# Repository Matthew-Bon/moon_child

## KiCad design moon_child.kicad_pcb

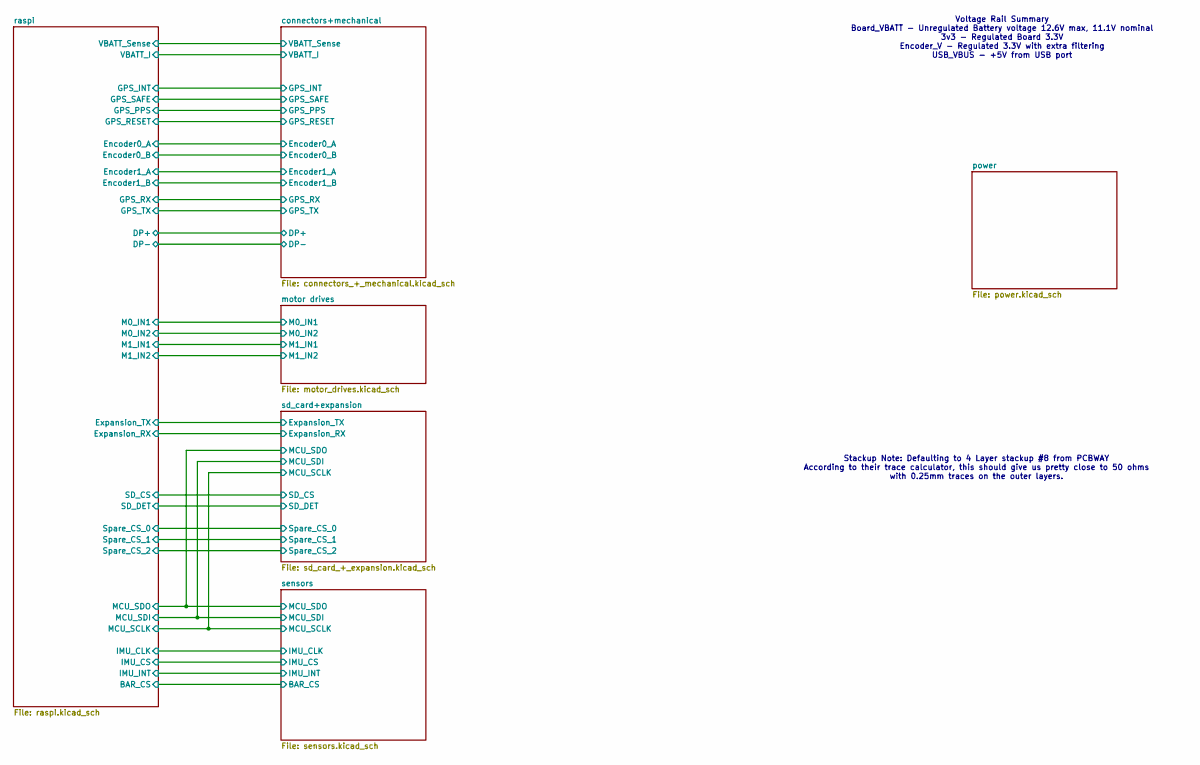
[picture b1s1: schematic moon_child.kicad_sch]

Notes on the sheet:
Voltage Rail Summary Board_VBATT - Unregulated Battery voltage 12.6V max, 11.1V nominal 3v3 - Regulated Board 3.3V Encoder_V - Regulated 3.3V with extra filtering USB_VBUS - +5V from USB port
Stackup Note: Defaulting to 4 Layer stackup #8 from PCBWAY According to their trace calculator, this should give us pretty close to 50 ohms with 0.25mm traces on the outer layers.

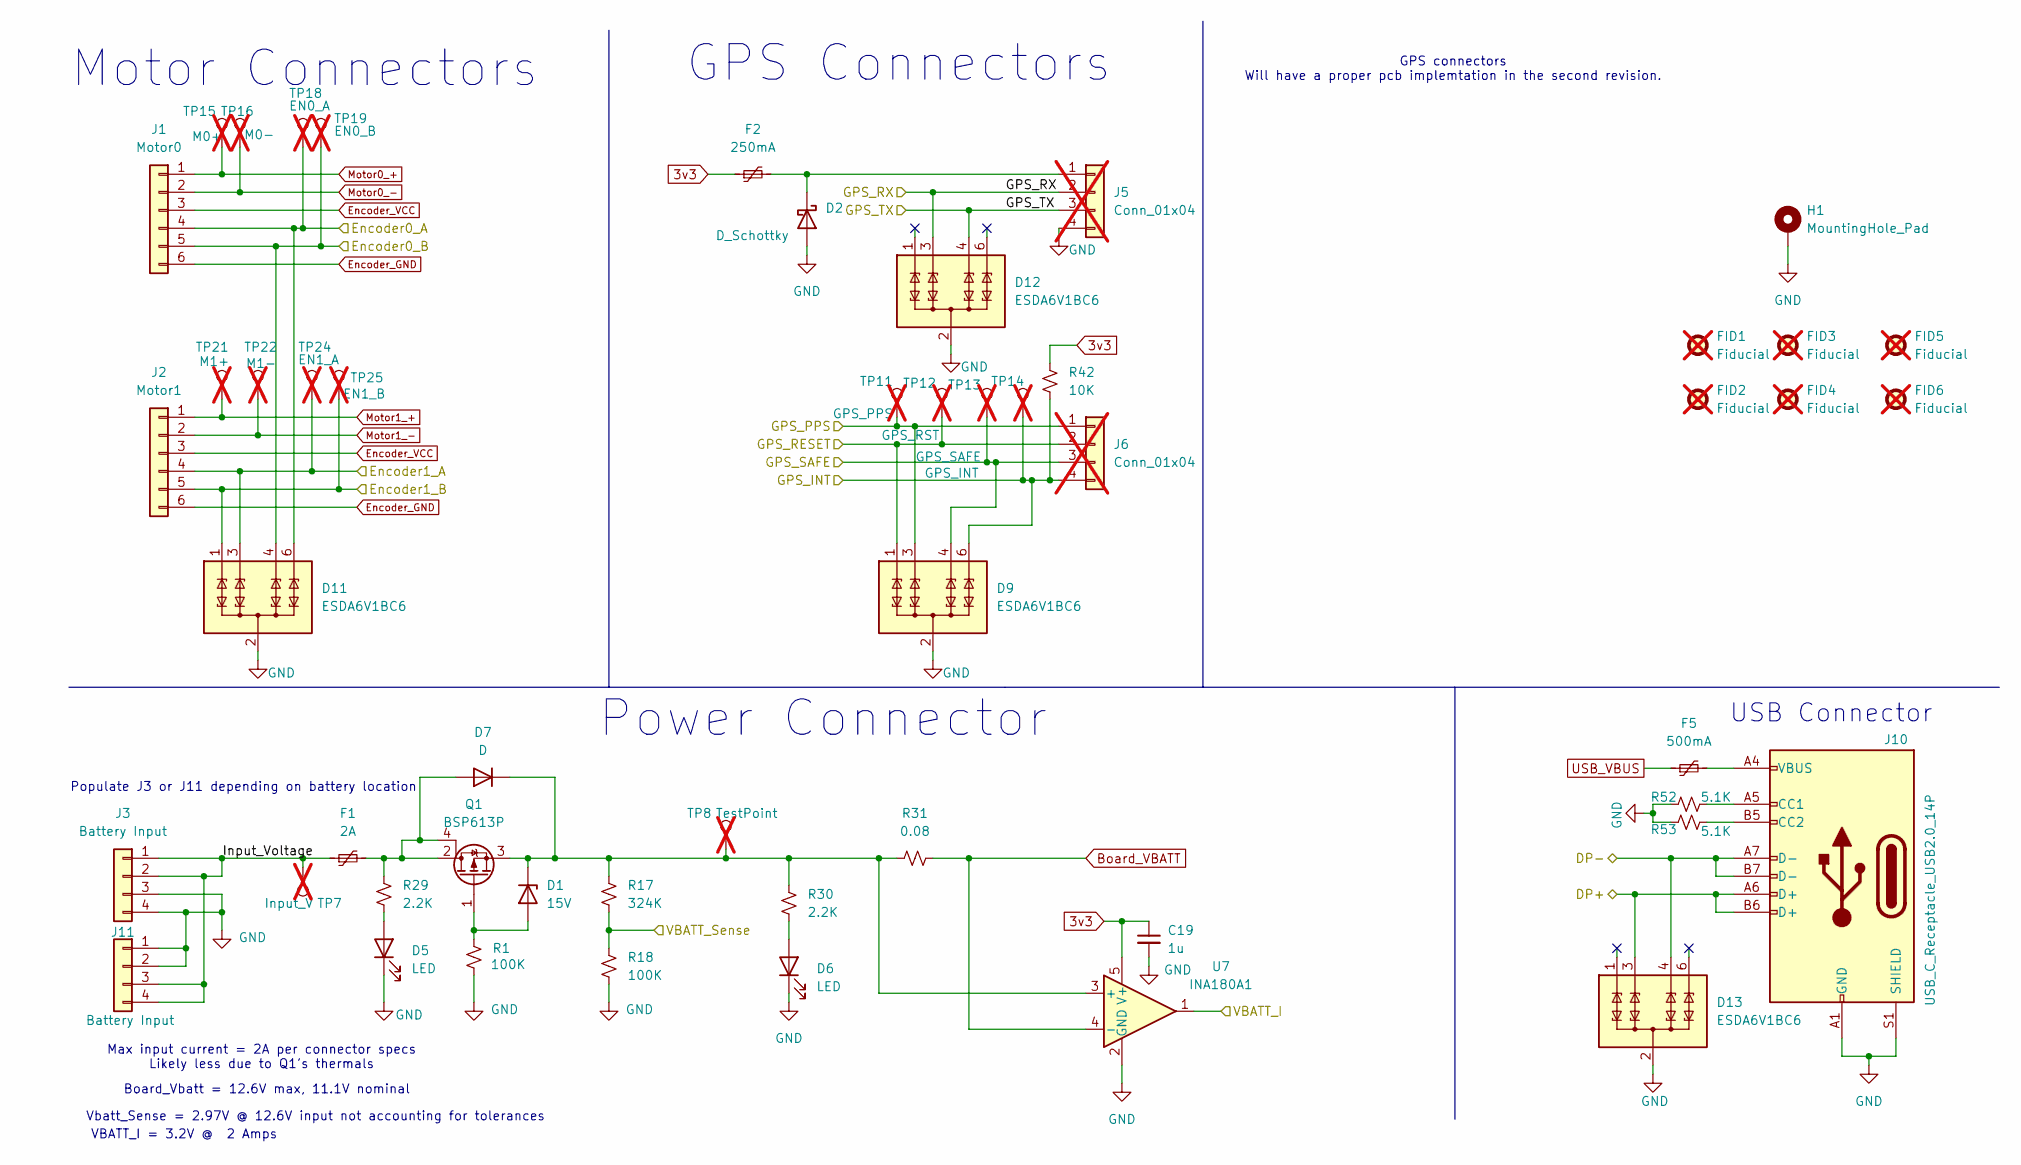
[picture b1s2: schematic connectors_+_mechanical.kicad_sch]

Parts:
C19: 1u; C_0603_1608Metric_Pad1.08x0.95mm_HandSolder; MPN CL10B105KP8NNNC
D1: 15V; D_SOD-323; MPN BZT52C15S-7-F
D2: D_Schottky; D_SOD-123; MPN MBR0530T1G
D5, D6: LED; D_0603_1608Metric_Pad1.05x0.95mm_HandSolder; MPN LTST-C190KFKT
D7: D; D_SMA; MPN S1J-13-F
D9, D11, D12, D13: ESDA6V1BC6; SOT-23-6; MPN ESDA6V1BC6
F1: 2A; Fuse_1206_3216Metric; MPN MF-NSML200/12-2
F2: 250mA; Fuse_1206_3216Metric; MPN 0ZCJ0025FF2E
F5: 500mA; Fuse_1206_3216Metric; MPN 0ZCJ0050AF2E
FID1, FID2, FID3, FID4, FID5, FID6: Fiducial; Fiducial_1mm_Mask2mm; not fitted
H1: MountingHole_Pad; MountingHole_4.3mm_M4_ISO14580_Pad
J1: Motor0; JST_SH_BM06B-SRSS-TB_1x06-1MP_P1.00mm_Vertical; MPN BM06B-SRSS-TB
J2: Motor1; JST_SH_BM06B-SRSS-TB_1x06-1MP_P1.00mm_Vertical; MPN BM06B-SRSS-TB
J3, J11: Battery Input; JST_SH_BM04B-SRSS-TB_1x04-1MP_P1.00mm_Vertical; MPN BM04B-SRSS-TB
J5, J6: Conn_01x04; PinHeader_1x04_P2.54mm_Vertical; not fitted
J10: USB_C_Receptacle_USB2.0_14P; GCT_USB4115-03-C_REVB4; MPN USB4115-03-C
Q1: BSP613P; SOT-223; MPN BSP613PH6327XTSA1
R1, R18: 100K; R_0402_1005Metric; MPN RC0402JR-07100KL
R17: 324K; R_0402_1005Metric; MPN RC0402FR-07324KL
R29, R30: 2.2K; R_0402_1005Metric; MPN RC0402JR-072K2L
R31: 0.08; R_1206_3216Metric; MPN RL1206FR-070R08L
R42: 10K; R_0402_1005Metric; MPN RC0402JR-0710KL
R52, R53: 5.1K; R_0402_1005Metric; MPN RC0402FR-075K1L
TP7: Input_V; TestPoint_Pad_D1.0mm; not fitted
TP8: TestPoint; TestPoint_Pad_D1.0mm; not fitted
TP11: GPS_PPS; TestPoint_Pad_D1.0mm; not fitted
TP12: GPS_RST; TestPoint_Pad_D1.0mm; not fitted
TP13: GPS_SAFE; TestPoint_Pad_D1.0mm; not fitted
TP14: GPS_INT; TestPoint_Pad_D1.0mm; not fitted
TP15: M0+; TestPoint_Pad_D1.0mm; not fitted
TP16: M0-; TestPoint_Pad_D1.0mm; not fitted
TP18: EN0_A; TestPoint_Pad_D1.0mm; not fitted
TP19: EN0_B; TestPoint_Pad_D1.0mm; not fitted
TP21: M1+; TestPoint_Pad_D1.0mm; not fitted
TP22: M1-; TestPoint_Pad_D1.0mm; not fitted
TP24: EN1_A; TestPoint_Pad_D1.0mm; not fitted
TP25: EN1_B; TestPoint_Pad_D1.0mm; not fitted
U7: INA180A1; SOT-23-5; MPN INA180A1IDBVR

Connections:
3v3: C19.1, F2.1, R42.1, U7.5 (V+); also elsewhere on the board
/connectors+mechanical/DP+: D13.3 (TVS2), J10.A6 (D+), J10.B6 (D+); also elsewhere on the board
/connectors+mechanical/DP-: D13.4 (TVS3), J10.A7 (D-), J10.B7 (D-); also elsewhere on the board
/connectors+mechanical/Encoder0_A: D11.6 (TVS4), J1.4, TP18.1; also elsewhere on the board
/connectors+mechanical/Encoder0_B: D11.4 (TVS3), J1.5, TP19.1; also elsewhere on the board
/connectors+mechanical/Encoder1_A: D11.3 (TVS2), J2.4, TP24.1; also elsewhere on the board
/connectors+mechanical/Encoder1_B: D11.1 (TVS1), J2.5, TP25.1; also elsewhere on the board
/connectors+mechanical/GPS_INT: D9.6 (TVS4), J6.4, R42.2, TP14.1; also elsewhere on the board
/connectors+mechanical/GPS_PPS: D9.3 (TVS2), J6.1, TP11.1; also elsewhere on the board
/connectors+mechanical/GPS_RESET: D9.1 (TVS1), J6.2, TP12.1; also elsewhere on the board
/connectors+mechanical/GPS_RX: D12.3 (TVS2), J5.2; also elsewhere on the board
/connectors+mechanical/GPS_SAFE: D9.4 (TVS3), J6.3, TP13.1; also elsewhere on the board
/connectors+mechanical/GPS_TX: D12.4 (TVS3), J5.3; also elsewhere on the board
/connectors+mechanical/Input_Voltage: F1.1, J3.1, J3.2, J11.3, J11.4, TP7.1
/connectors+mechanical/VBATT_I: U7.1; also elsewhere on the board
/connectors+mechanical/VBATT_Sense: R17.2, R18.1; also elsewhere on the board
Board_VBATT: R31.2, U7.4 (-); also elsewhere on the board
Encoder_GND: J1.6, J2.6; also elsewhere on the board
Encoder_VCC: J1.3, J2.3; also elsewhere on the board
GND: C19.2, D2.2 (A), D5.1 (K), D6.1 (K), D9.2 (COM), D9.5 (COM), D11.2 (COM), D11.5 (COM), D12.2 (COM), D12.5 (COM), D13.2 (COM), D13.5 (COM), H1.1, J3.3, J3.4, J5.4, J10.A1 (GND), J10.A12 (GND), J10.B1 (GND), J10.B12 (GND), J10.S1 (SHIELD), J11.1, J11.2, R1.2, R18.2, R52.1, R53.1, U7.2 (GND); also elsewhere on the board
Motor0_+: J1.1, TP15.1; also elsewhere on the board
Motor0_-: J1.2, TP16.1; also elsewhere on the board
Motor1_+: J2.1, TP21.1; also elsewhere on the board
Motor1_-: J2.2, TP22.1; also elsewhere on the board
unnamed: D1.2 (A), Q1.1 (G), R1.1
unnamed: D1.1 (K), D7.1 (K), Q1.3 (S), R17.1, R30.1, R31.1, TP8.1, U7.3 (+)
unnamed: D2.1 (K), F2.2, J5.1
unnamed: D5.2 (A), R29.2
unnamed: D6.2 (A), R30.2
unnamed: D7.2 (A), F1.2, Q1.2 (D), Q1.4 (D), R29.1
unnamed: F5.2, J10.A4 (VBUS), J10.A9 (VBUS), J10.B4 (VBUS), J10.B9 (VBUS)
unnamed: J10.A5 (CC1), R52.2
unnamed: J10.B5 (CC2), R53.2
USB_VBUS: F5.1; also elsewhere on the board

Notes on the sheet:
Populate J3 or J11 depending on battery location
Board_Vbatt = 12.6V max, 11.1V nominal
Motor Connectors
GPS Connectors
USB Connector
Vbatt_Sense = 2.97V @ 12.6V input not accounting for tolerances
GPS connectors Will have a proper pcb implemtation in the second revision.
VBATT_I = 3.2V @ 2 Amps
Power Connector
Max input current = 2A per connector specs Likely less due to Q1's thermals

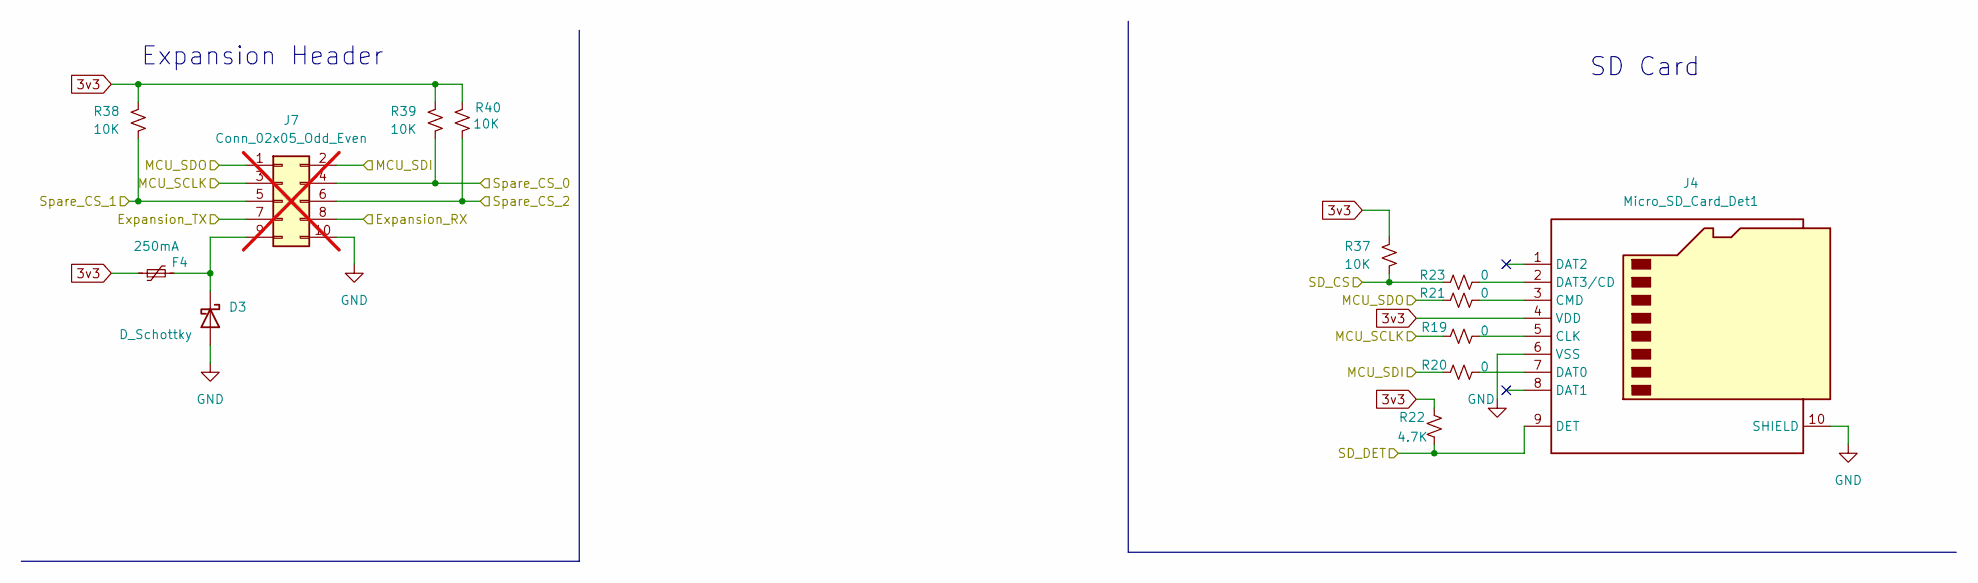
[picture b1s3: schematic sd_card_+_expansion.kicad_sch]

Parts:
D3: D_Schottky; D_SOD-123; MPN MBR0530T1G
F4: 250mA; Fuse_1206_3216Metric; MPN 0ZCJ0025FF2E
J4: Micro_SD_Card_Det1; microSD_HC_Hirose_DM3D-SF; MPN DM3D-SF
J7: Conn_02x05_Odd_Even; PinHeader_2x05_P2.54mm_Vertical_SMD; not fitted
R19, R20, R21, R23: 0; R_0402_1005Metric; MPN RC0402FR-070RL
R22: 4.7K; R_0402_1005Metric; MPN RC0402JR-074K7L
R37, R38, R39, R40: 10K; R_0402_1005Metric; MPN RC0402JR-0710KL

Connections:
3v3: F4.1, J4.4 (VDD), R22.1, R37.1, R38.1, R39.1, R40.1; also elsewhere on the board
/raspi/Expansion_RX: J7.8; also elsewhere on the board
/raspi/Expansion_TX: J7.7; also elsewhere on the board
/raspi/SD_CS: R23.1, R37.2; also elsewhere on the board
/raspi/SD_DET: J4.9 (DET), R22.2; also elsewhere on the board
/raspi/Spare_CS_0: J7.4, R39.2; also elsewhere on the board
/raspi/Spare_CS_1: J7.5, R38.2; also elsewhere on the board
/raspi/Spare_CS_2: J7.6, R40.2; also elsewhere on the board
/sensors/MCU_SCLK: J7.3, R19.1; also elsewhere on the board
/sensors/MCU_SDI: J7.2, R20.1; also elsewhere on the board
/sensors/MCU_SDO: J7.1, R21.1; also elsewhere on the board
GND: D3.2 (A), J4.6 (VSS), J4.10 (SHIELD), J7.10; also elsewhere on the board
unnamed: D3.1 (K), F4.2, J7.9
unnamed: J4.5 (CLK), R19.2
unnamed: J4.3 (CMD), R21.2
unnamed: J4.7 (DAT0), R20.2
unnamed: J4.2 (DAT3/CD), R23.2

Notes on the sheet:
Expansion Header
SD Card

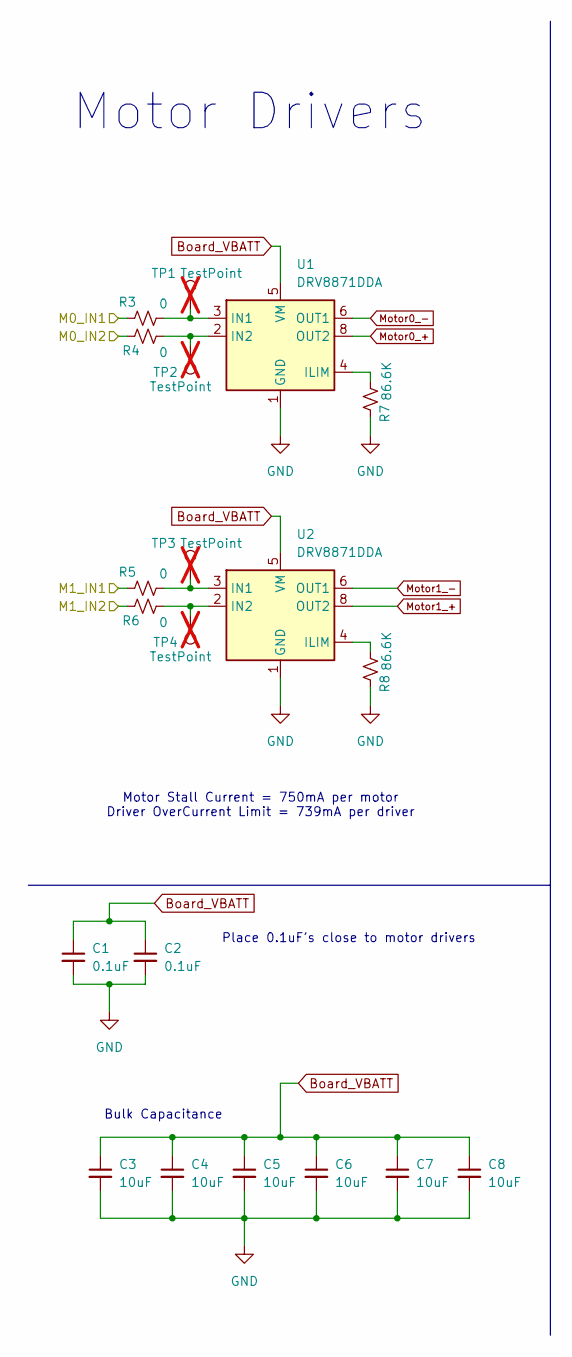
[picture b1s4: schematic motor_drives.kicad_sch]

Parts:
C1, C2: 0.1uF; C_0603_1608Metric_Pad1.08x0.95mm_HandSolder; MPN CC0603KRX7R7BB104
C3, C4, C5, C6, C7, C8: 10uF; C_0805_2012Metric_Pad1.18x1.45mm_HandSolder; MPN CL21A106KOQNNNE
R3, R4, R5, R6: 0; R_0402_1005Metric; MPN RC0402FR-070RL
R7, R8: 86.6K; R_0402_1005Metric; MPN CRCW040286K6FKEDC
TP1, TP2, TP3, TP4: TestPoint; TestPoint_Pad_D1.0mm; not fitted
U1, U2: DRV8871DDA; Texas_HTSOP-8-1EP_3.9x4.9mm_P1.27mm_EP2.95x4.9mm_Mask2.4x3.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; MPN DRV8871DDAR

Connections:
/motor drives/M0_IN1: R3.1; also elsewhere on the board
/motor drives/M0_IN2: R4.2; also elsewhere on the board
/motor drives/M1_IN1: R5.1; also elsewhere on the board
/motor drives/M1_IN2: R6.2; also elsewhere on the board
Board_VBATT: C1.1, C2.1, C3.1, C4.1, C5.1, C6.1, C7.1, C8.1, U1.5 (VM), U2.5 (VM); also elsewhere on the board
GND: C1.2, C2.2, C3.2, C4.2, C5.2, C6.2, C7.2, C8.2, R7.2, R8.2, U1.1 (GND), U1.7 (GND), U1.9 (GND), U2.1 (GND), U2.7 (GND), U2.9 (GND); also elsewhere on the board
Motor0_+: U1.8 (OUT2); also elsewhere on the board
Motor0_-: U1.6 (OUT1); also elsewhere on the board
Motor1_+: U2.8 (OUT2); also elsewhere on the board
Motor1_-: U2.6 (OUT1); also elsewhere on the board
unnamed: R7.1, U1.4 (ILIM)
unnamed: R3.2, TP1.1, U1.3 (IN1)
unnamed: R4.1, TP2.1, U1.2 (IN2)
unnamed: R8.1, U2.4 (ILIM)
unnamed: R5.2, TP3.1, U2.3 (IN1)
unnamed: R6.1, TP4.1, U2.2 (IN2)

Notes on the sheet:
Bulk Capacitance
Motor Drivers
Motor Stall Current = 750mA per motor Driver OverCurrent Limit = 739mA per driver
Place 0.1uF's close to motor drivers

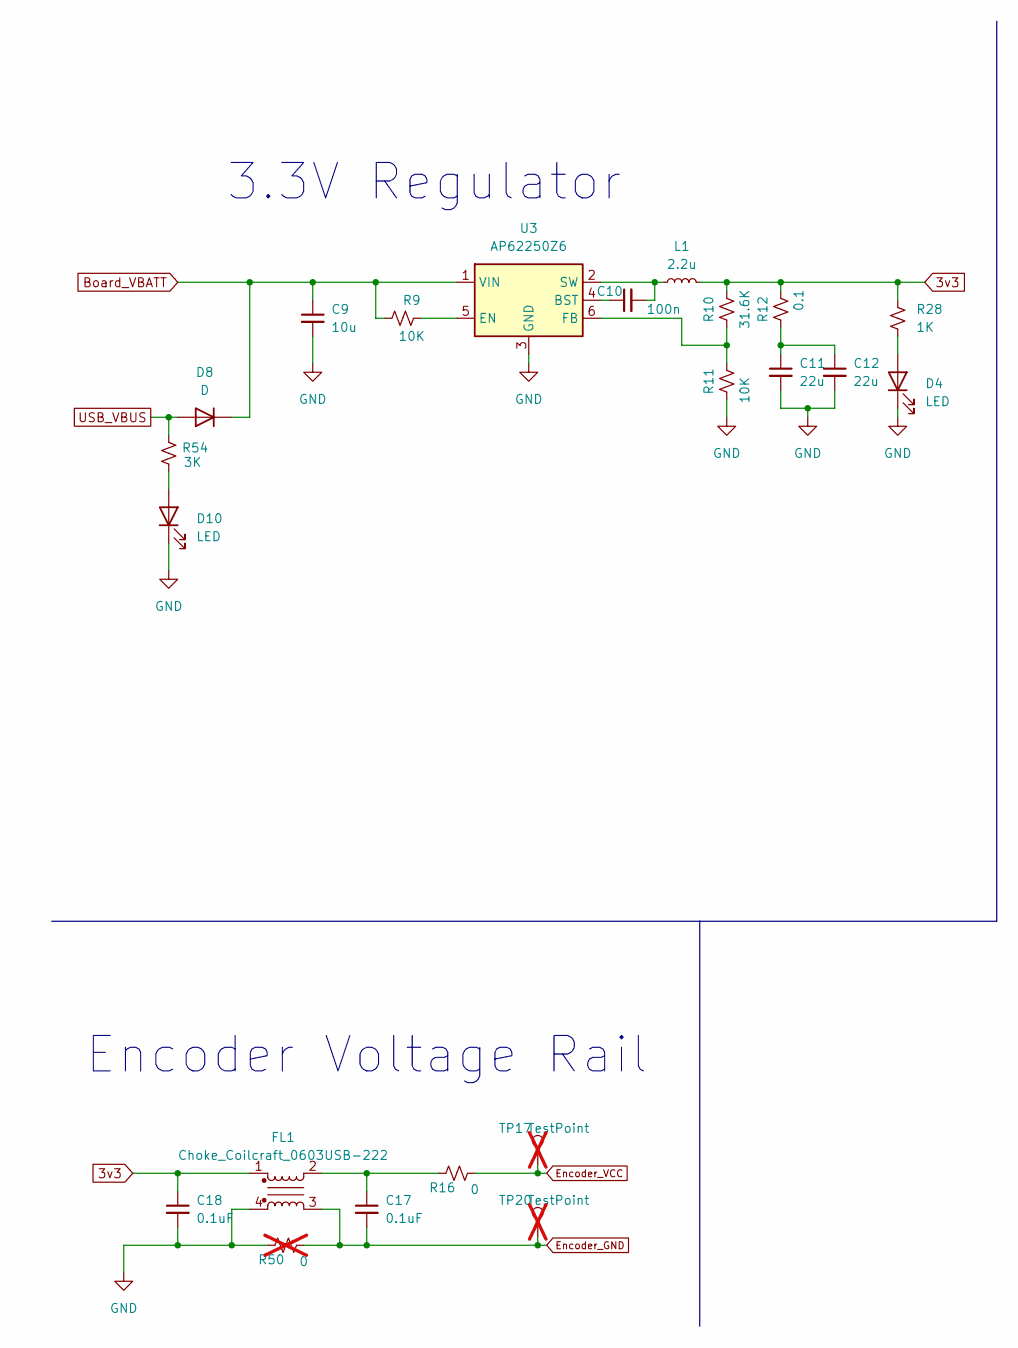
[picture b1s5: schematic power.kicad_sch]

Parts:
C9: 10u; C_0805_2012Metric; MPN CL21A106KOQNNNE
C10: 100n; C_0402_1005Metric; MPN CL05B104KP5NNNC
C11, C12: 22u; C_0805_2012Metric; MPN CL21A226MAYNNNE
C17, C18: 0.1uF; C_0603_1608Metric_Pad1.08x0.95mm_HandSolder; MPN CC0603KRX7R7BB104
D4, D10: LED; D_0603_1608Metric_Pad1.05x0.95mm_HandSolder; MPN LTST-C190KFKT
D8: D; D_SMA; MPN S1J-13-F
FL1: Choke_Coilcraft_0603USB-222; L_CommonModeChoke_Coilcraft_0603USB; MPN 0603USB-222MLC
L1: 2.2u; L_Bourns_SRP5030T; MPN SRP5030TA-2R2M
R9, R11: 10K; R_0402_1005Metric; MPN RC0402JR-0710KL
R10: 31.6K; R_0402_1005Metric; MPN RT0402FRE0731K6L
R12: 0.1; R_0805_2012Metric; MPN ERJ-6DSFR10V
R16: 0; R_0402_1005Metric; MPN RC0402FR-070RL
R28: 1K; R_0402_1005Metric; MPN RC0402JR-071KL
R50: 0; R_0402_1005Metric; MPN RC0402FR-070RL; not fitted
R54: 3K; R_0402_1005Metric; MPN ERA-2AEB302X
TP17, TP20: TestPoint; TestPoint_Pad_D1.0mm; not fitted
U3: AP62250Z6; SOT-563; MPN AP62250Z6-7

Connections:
3v3: C18.1, FL1.1, L1.2, R10.2, R12.2, R28.1; also elsewhere on the board
Board_VBATT: C9.1, D8.1 (K), R9.1, U3.1 (VIN); also elsewhere on the board
Encoder_GND: C17.2, FL1.3, R50.1, TP20.1; also elsewhere on the board
Encoder_VCC: R16.1, TP17.1; also elsewhere on the board
GND: C9.2, C11.2, C12.2, C18.2, D4.1 (K), D10.1 (K), FL1.4, R11.1, R50.2, U3.3 (GND); also elsewhere on the board
unnamed: C11.1, C12.1, R12.1
unnamed: C17.1, FL1.2, R16.2
unnamed: D4.2 (A), R28.2
unnamed: D10.2 (A), R54.2
unnamed: C10.1, U3.4 (BST)
unnamed: R9.2, U3.5 (EN)
unnamed: R10.1, R11.2, U3.6 (FB)
unnamed: C10.2, L1.1, U3.2 (SW)
USB_VBUS: D8.2 (A), R54.1; also elsewhere on the board

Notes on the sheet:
3.3V Regulator
Encoder Voltage Rail

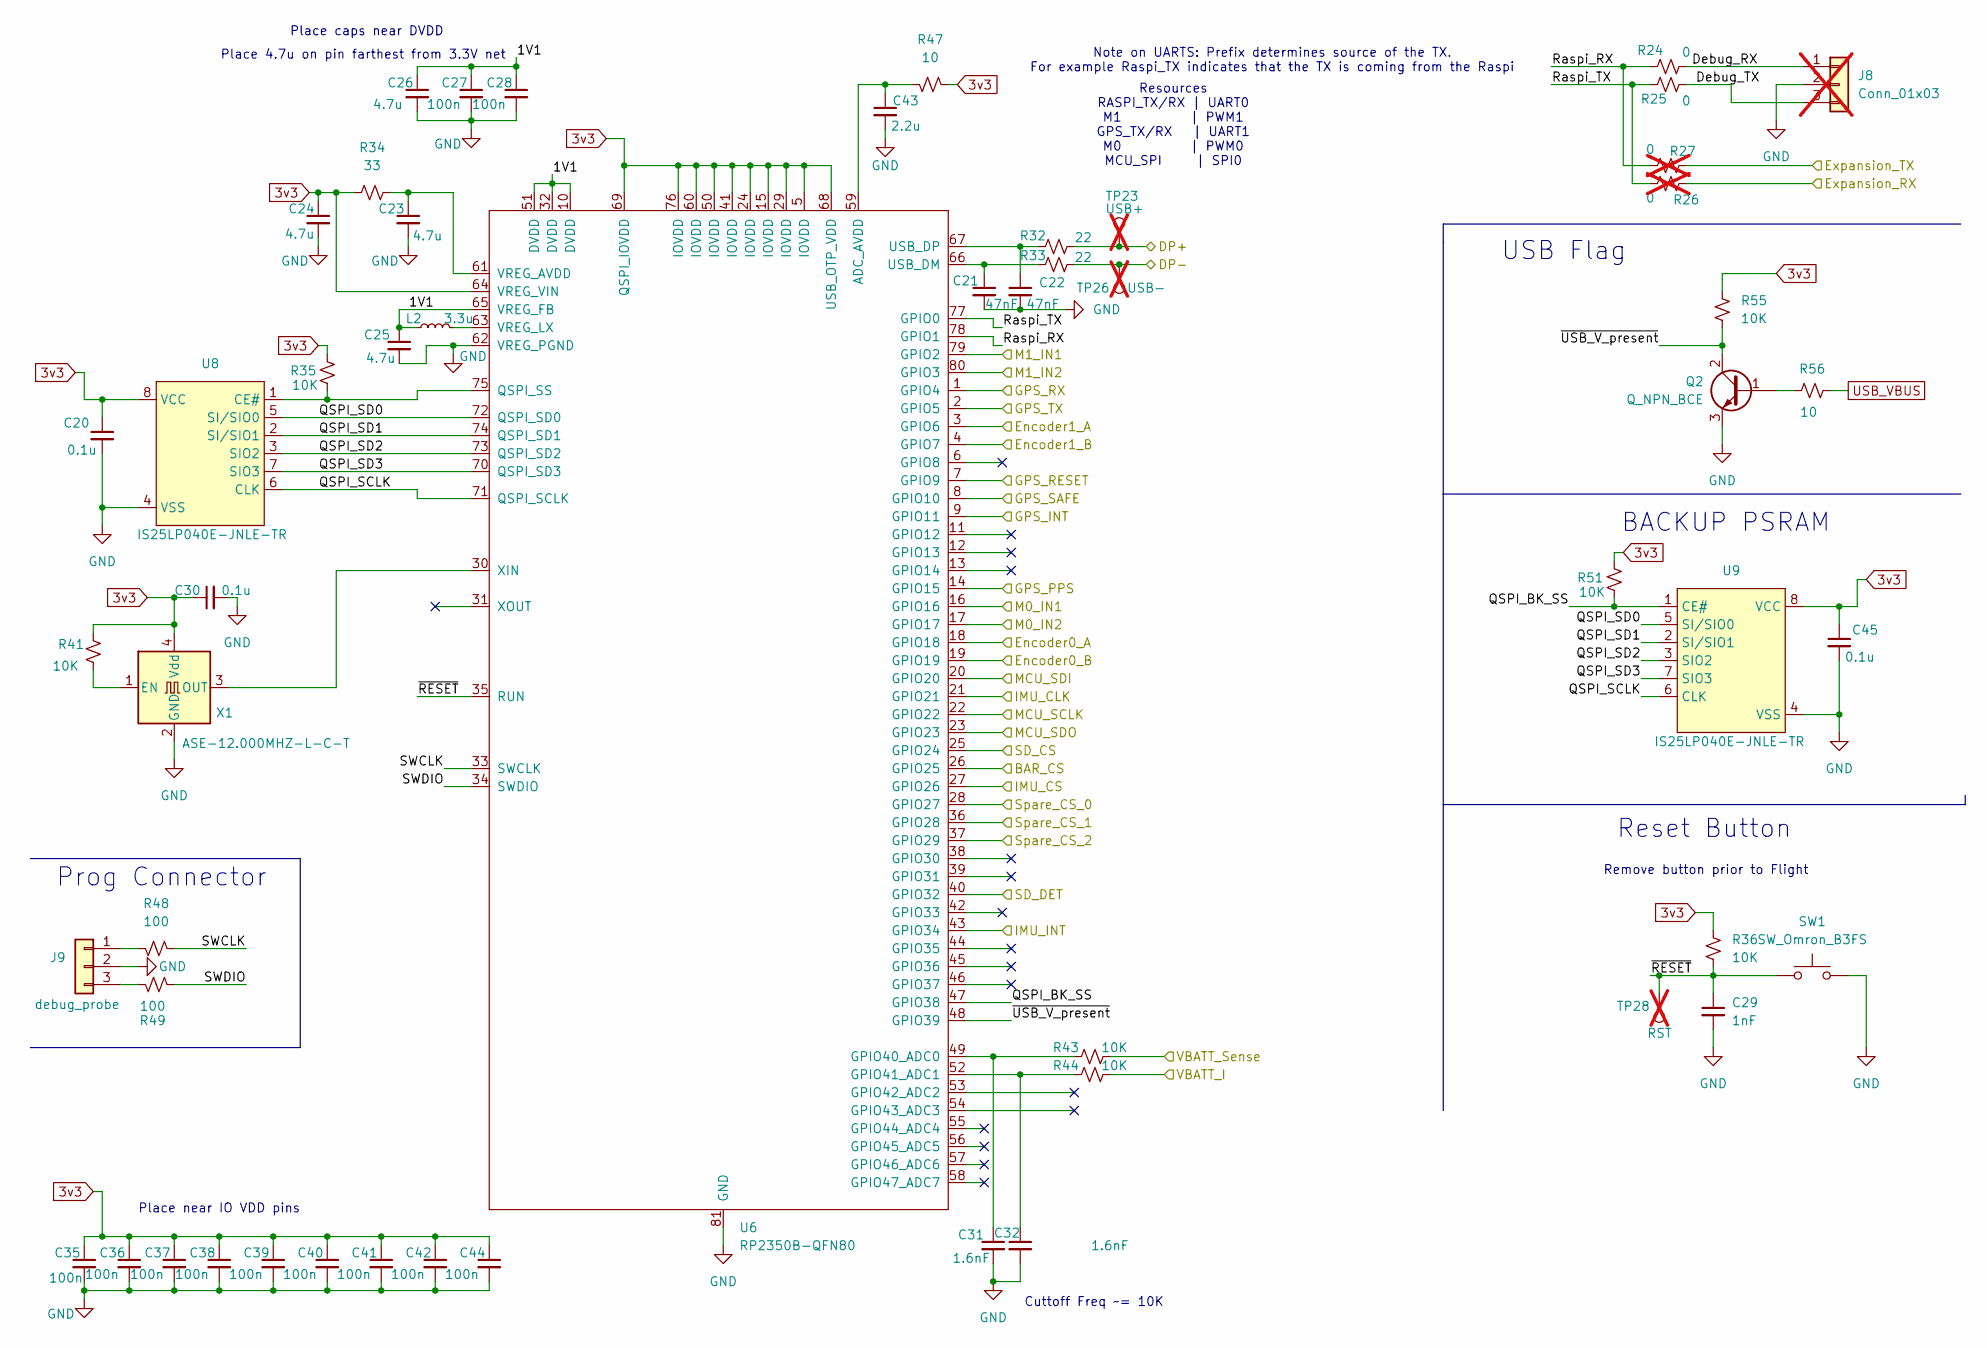
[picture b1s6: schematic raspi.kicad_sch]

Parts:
C20, C30, C45: 0.1u; C_0603_1608Metric_Pad1.08x0.95mm_HandSolder; MPN CC0603KRX7R7BB104
C21, C22: 47nF; C_0603_1608Metric_Pad1.08x0.95mm_HandSolder; MPN CL10B473KO8NNNC
C23, C24, C25, C26: 4.7u; C_0805_2012Metric_Pad1.18x1.45mm_HandSolder; MPN CL21A475KAQNNNE
C27, C28, C35, C36, C37, C38, C39, C40, C41, C42, C44: 100n; C_0603_1608Metric_Pad1.08x0.95mm_HandSolder; MPN CC0603KRX7R7BB104
C29: 1nF; C_0603_1608Metric_Pad1.08x0.95mm_HandSolder; MPN CL10B102KB8NNNC
C31, C32: 1.6nF; C_0603_1608Metric_Pad1.08x0.95mm_HandSolder; MPN GRM1885C1H162JA01D
C43: 2.2u; C_0603_1608Metric_Pad1.08x0.95mm_HandSolder; MPN CL10A225KO8NNNC
J8: Conn_01x03; PinHeader_1x03_P2.54mm_Vertical; not fitted
J9: debug_probe; JST_SH_BM03B-SRSS-TB_1x03-1MP_P1.00mm_Vertical; MPN BM03B-SRSS-TB
L2: 3.3u; L_1008_2520Metric; MPN TFM252012ALMA3R3MTAA
Q2: Q_NPN_BCE; SOT-23-3; MPN MMBT3904-7-F
R24, R25: 0; R_0402_1005Metric; MPN RC0402FR-070RL
R26, R27: 0; R_0402_1005Metric; MPN RC0402FR-070RL; not fitted
R32, R33: 22; R_0402_1005Metric; MPN RC0402FR-0722RL
R34: 33; R_0402_1005Metric; MPN RC0402JR-0733RL
R35, R36, R41, R43, R44, R51, R55: 10K; R_0402_1005Metric; MPN RC0402JR-0710KL
R47, R56: 10; R_0402_1005Metric; MPN RC0402FR-0710RL
R48, R49: 100; R_0402_1005Metric; MPN RC0402FR-07100RL
SW1: SW_Omron_B3FS; SW_SPST_B3S-1000; MPN B3FS-1002P
TP23: USB+; TestPoint_Pad_D1.0mm; not fitted
TP26: USB-; TestPoint_Pad_D1.0mm; not fitted
TP28: RST; TestPoint_Pad_D1.0mm; not fitted
U6: RP2350B-QFN80; RP2350B_QFN-80_EP_10.573x10.573_Pitch0.4mm; MPN SC1510-A4
U8, U9: IS25LP040E-JNLE-TR; SOIC-8_3.9x4.9mm_P1.27mm; MPN IS25LP040E-JNLE-TR
X1: ASE-12.000MHZ-L-C-T; Oscillator_SMD_Abracon_ASE-4Pin_3.2x2.5mm; MPN ASE-12.000MHZ-L-C-T

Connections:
3v3: C20.1, C24.1, C30.1, C35.1, C36.1, C37.1, C38.1, C39.1, C40.1, C41.1, C42.1, C44.1, C45.1, R34.1, R35.1, R36.1, R41.1, R47.1, R51.1, R55.1, U6.5 (IOVDD), U6.15 (IOVDD), U6.24 (IOVDD), U6.29 (IOVDD), U6.41 (IOVDD), U6.50 (IOVDD), U6.60 (IOVDD), U6.64 (VREG_VIN), U6.68 (USB_OTP_VDD), U6.69 (QSPI_IOVDD), U6.76 (IOVDD), U8.8 (VCC), U9.8 (VCC), X1.4 (Vdd); also elsewhere on the board
/connectors+mechanical/DP+: R32.2, TP23.1; also elsewhere on the board
/connectors+mechanical/DP-: R33.2, TP26.1; also elsewhere on the board
/connectors+mechanical/Encoder0_A: U6.18 (GPIO18); also elsewhere on the board
/connectors+mechanical/Encoder0_B: U6.19 (GPIO19); also elsewhere on the board
/connectors+mechanical/Encoder1_A: U6.3 (GPIO6); also elsewhere on the board
/connectors+mechanical/Encoder1_B: U6.4 (GPIO7); also elsewhere on the board
/connectors+mechanical/GPS_INT: U6.9 (GPIO11); also elsewhere on the board
/connectors+mechanical/GPS_PPS: U6.14 (GPIO15); also elsewhere on the board
/connectors+mechanical/GPS_RESET: U6.7 (GPIO9); also elsewhere on the board
/connectors+mechanical/GPS_RX: U6.1 (GPIO4); also elsewhere on the board
/connectors+mechanical/GPS_SAFE: U6.8 (GPIO10); also elsewhere on the board
/connectors+mechanical/GPS_TX: U6.2 (GPIO5); also elsewhere on the board
/connectors+mechanical/VBATT_I: R44.2; also elsewhere on the board
/connectors+mechanical/VBATT_Sense: R43.2; also elsewhere on the board
/motor drives/M0_IN1: U6.16 (GPIO16); also elsewhere on the board
/motor drives/M0_IN2: U6.17 (GPIO17); also elsewhere on the board
/motor drives/M1_IN1: U6.79 (GPIO2); also elsewhere on the board
/motor drives/M1_IN2: U6.80 (GPIO3); also elsewhere on the board
/raspi/1V1: C25.1, C26.1, C27.1, C28.1, L2.1, U6.10 (DVDD), U6.32 (DVDD), U6.51 (DVDD), U6.65 (VREG_FB)
/raspi/BAR_CS: U6.26 (GPIO25); also elsewhere on the board
/raspi/Debug_RX: J8.1, R24.2
/raspi/Debug_TX: J8.3, R25.1
/raspi/Expansion_RX: R26.1; also elsewhere on the board
/raspi/Expansion_TX: R27.2; also elsewhere on the board
/raspi/IMU_CLK: U6.21 (GPIO21); also elsewhere on the board
/raspi/IMU_CS: U6.27 (GPIO26); also elsewhere on the board
/raspi/IMU_INT: U6.43 (GPIO34); also elsewhere on the board
/raspi/QSPI_BK_SS: R51.2, U6.47 (GPIO38), U9.1 (CE#)
/raspi/QSPI_SCLK: U6.71 (QSPI_SCLK), U8.6 (CLK), U9.6 (CLK)
/raspi/QSPI_SD0: U6.72 (QSPI_SD0), U8.5 (SI/SIO0), U9.5 (SI/SIO0)
/raspi/QSPI_SD1: U6.74 (QSPI_SD1), U8.2 (SI/SIO1), U9.2 (SI/SIO1)
/raspi/QSPI_SD2: U6.73 (QSPI_SD2), U8.3 (SIO2), U9.3 (SIO2)
/raspi/QSPI_SD3: U6.70 (QSPI_SD3), U8.7 (SIO3), U9.7 (SIO3)
/raspi/Raspi_RX: R24.1, R27.1, U6.78 (GPIO1)
/raspi/Raspi_TX: R25.2, R26.2, U6.77 (GPIO0)
/raspi/SD_CS: U6.25 (GPIO24); also elsewhere on the board
/raspi/SD_DET: U6.40 (GPIO32); also elsewhere on the board
/raspi/SWCLK: R48.1, U6.33 (SWCLK)
/raspi/SWDIO: R49.1, U6.34 (SWDIO)
/raspi/Spare_CS_0: U6.28 (GPIO27); also elsewhere on the board
/raspi/Spare_CS_1: U6.36 (GPIO28); also elsewhere on the board
/raspi/Spare_CS_2: U6.37 (GPIO29); also elsewhere on the board
/raspi/~RESET: C29.1, R36.2, SW1.1, TP28.1, U6.35 (RUN)
/raspi/~USB_V_present: Q2.2 (C), R55.2, U6.48 (GPIO39)
/sensors/MCU_SCLK: U6.22 (GPIO22); also elsewhere on the board
/sensors/MCU_SDI: U6.20 (GPIO20); also elsewhere on the board
/sensors/MCU_SDO: U6.23 (GPIO23); also elsewhere on the board
GND: C20.2, C21.2, C22.2, C23.2, C24.2, C25.2, C26.2, C27.2, C28.2, C29.2, C30.2, C31.2, C32.2, C35.2, C36.2, C37.2, C38.2, C39.2, C40.2, C41.2, C42.2, C43.2, C44.2, C45.2, J8.2, J9.2, Q2.3 (E), SW1.2, U6.62 (VREG_PGND), U6.81 (GND), U8.4 (VSS), U9.4 (VSS), X1.2 (GND); also elsewhere on the board
unnamed: J9.1, R48.2
unnamed: J9.3, R49.2
unnamed: Q2.1 (B), R56.1
unnamed: C43.1, R47.2, U6.59 (ADC_AVDD)
unnamed: C31.1, R43.1, U6.49 (GPIO40_ADC0)
unnamed: C32.1, R44.1, U6.52 (GPIO41_ADC1)
unnamed: R35.2, U6.75 (QSPI_SS), U8.1 (CE#)
unnamed: C21.1, R33.1, U6.66 (USB_DM)
unnamed: C22.1, R32.1, U6.67 (USB_DP)
unnamed: C23.1, R34.2, U6.61 (VREG_AVDD)
unnamed: L2.2, U6.63 (VREG_LX)
unnamed: U6.30 (XIN), X1.3 (OUT)
unnamed: R41.2, X1.1 (EN)
USB_VBUS: R56.2; also elsewhere on the board

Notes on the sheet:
USB Flag
Place near IO VDD pins
Resources RASPI_TX/RX | UART0 M1 | PWM1 GPS_TX/RX | UART1 M0 | PWM0 MCU_SPI | SPI0
Note on UARTS: Prefix determines source of the TX. For example Raspi_TX indicates that the TX is coming from the Raspi
Reset Button
Cuttoff Freq ~= 10K
Remove button prior to Flight
BACKUP PSRAM
Place 4.7u on pin farthest from 3.3V net
Place caps near DVDD
Prog Connector

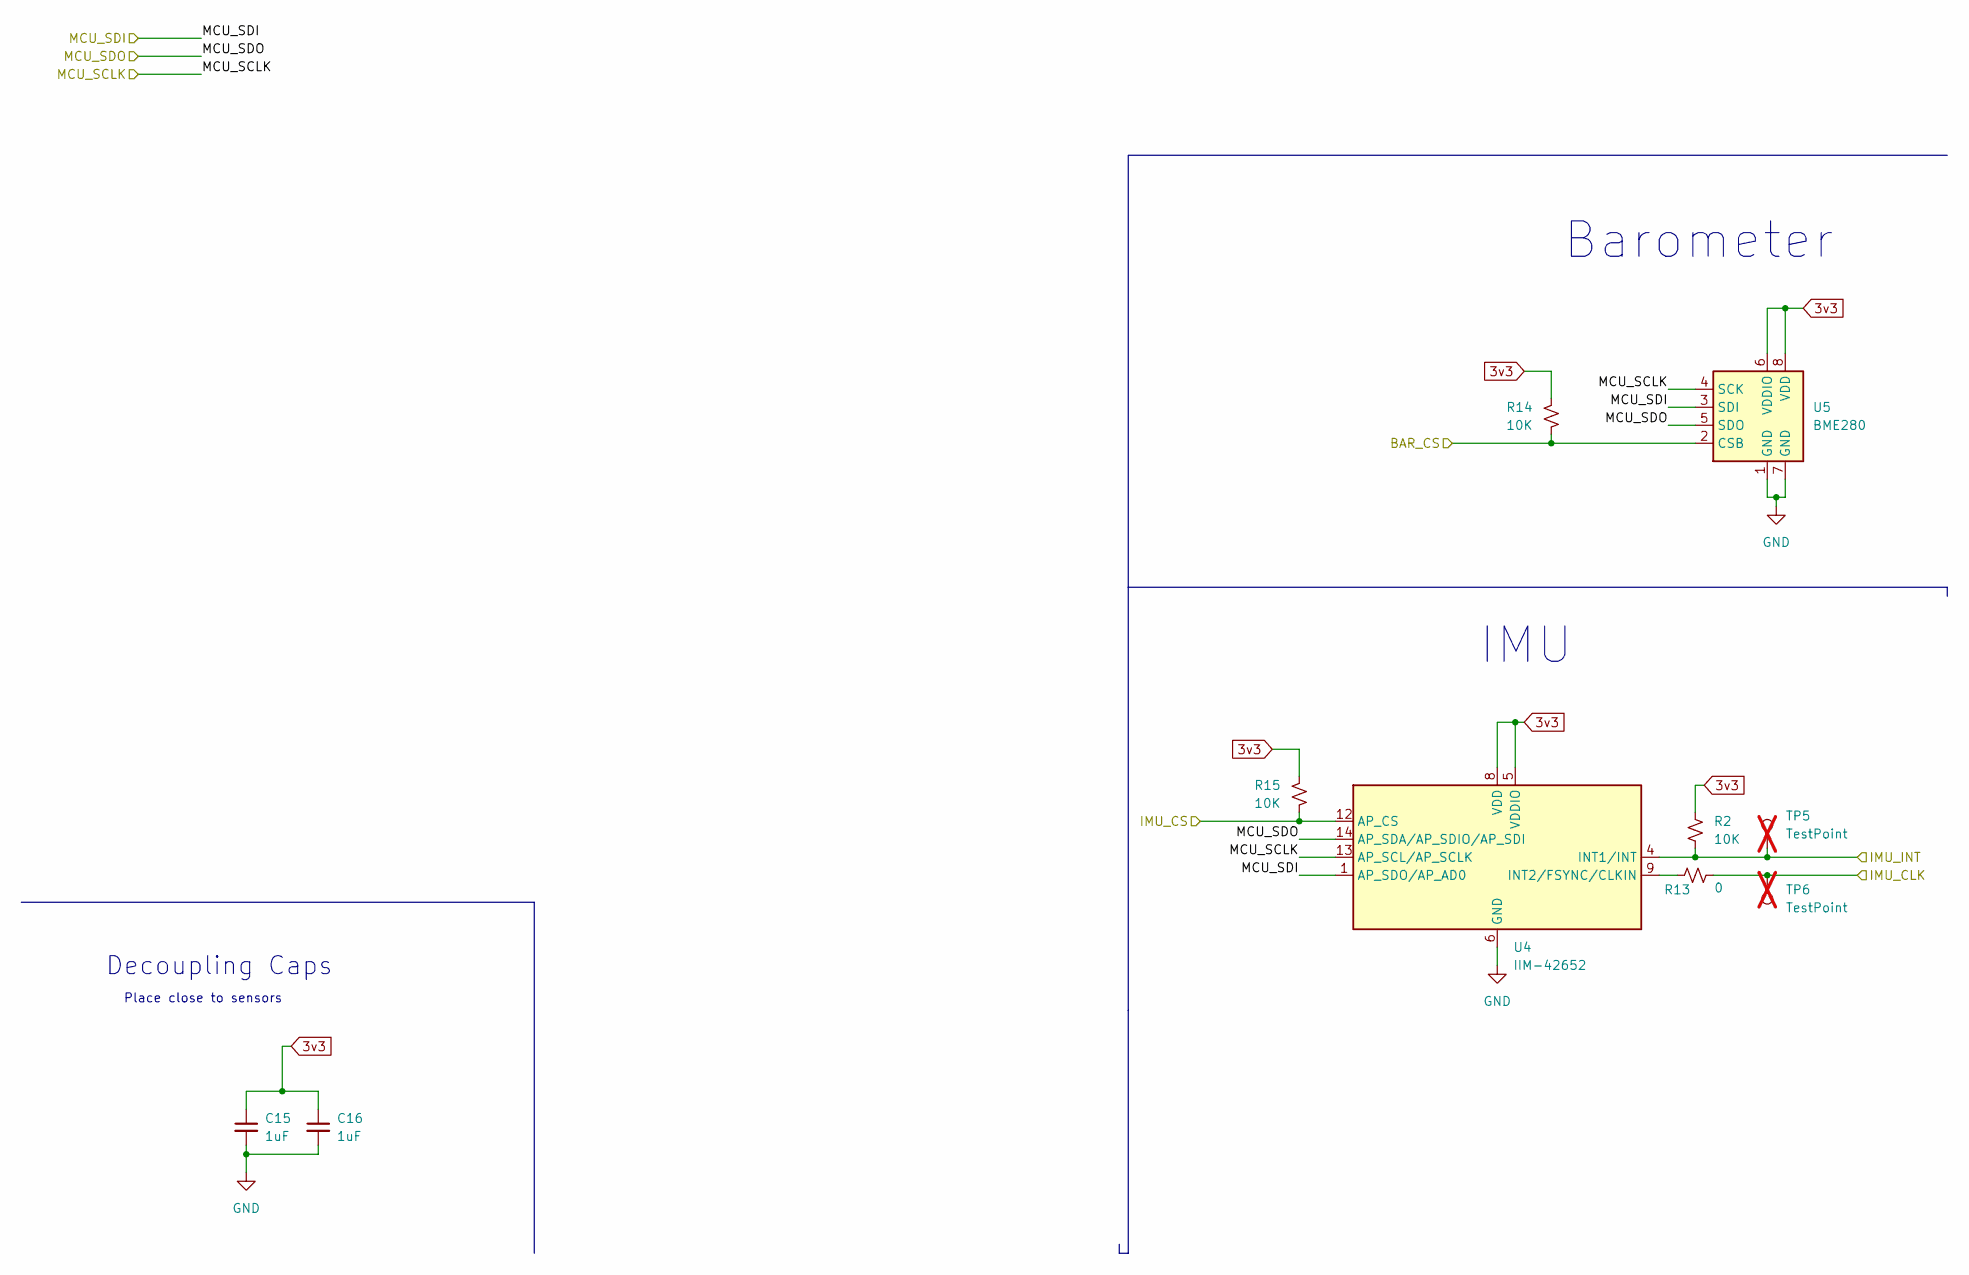
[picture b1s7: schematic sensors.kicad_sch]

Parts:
C15, C16: 1uF; C_0603_1608Metric_Pad1.08x0.95mm_HandSolder; MPN CL10B105KP8NNNC
R2, R14, R15: 10K; R_0402_1005Metric; MPN RC0402JR-0710KL
R13: 0; R_0402_1005Metric; MPN RC0402FR-070RL
TP5, TP6: TestPoint; TestPoint_Pad_D1.0mm; not fitted
U4: IIM-42652; Bosch_LGA-14_3x2.5mm_P0.5mm; MPN IIM-42652
U5: BME280; Bosch_LGA-8_2x2.5mm_P0.65mm_ClockwisePinNumbering; MPN BME280

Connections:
3v3: C15.1, C16.1, R2.1, R14.1, R15.1, U4.5 (VDDIO), U4.8 (VDD), U5.6 (VDDIO), U5.8 (VDD); also elsewhere on the board
/raspi/BAR_CS: R14.2, U5.2 (CSB); also elsewhere on the board
/raspi/IMU_CLK: R13.1, TP6.1; also elsewhere on the board
/raspi/IMU_CS: R15.2, U4.12 (AP_CS); also elsewhere on the board
/raspi/IMU_INT: R2.2, TP5.1, U4.4 (INT1/INT); also elsewhere on the board
/sensors/MCU_SCLK: U4.13 (AP_SCL/AP_SCLK), U5.4 (SCK); also elsewhere on the board
/sensors/MCU_SDI: U4.1 (AP_SDO/AP_AD0), U5.3 (SDI); also elsewhere on the board
/sensors/MCU_SDO: U4.14 (AP_SDA/AP_SDIO/AP_SDI), U5.5 (SDO); also elsewhere on the board
GND: C15.2, C16.2, U4.6 (GND), U4.7 (GND), U5.1 (GND), U5.7 (GND); also elsewhere on the board
unnamed: R13.2, U4.9 (INT2/FSYNC/CLKIN)

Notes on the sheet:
IMU
Decoupling Caps
Barometer
Place close to sensors
